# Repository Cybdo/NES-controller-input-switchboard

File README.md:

# NES-controller-input-switchboard
The switchboard is essentially a 2:2 6-channel multiplexer, with one output being routed to an RP2040 for processing and a USB Keyboard output as opposed to exposing it directly.
Part of a larger homemade arcade project, I want to be able to have a embedded controller with arcade buttons and an external connector for external controllers or a light zapper, to be routed to an NES for retro games, as well as a ZimaBoard or Pi 4 (or other computer, via USB) for modern games

## Features:
- 6 channel 2:2 multiplexer
- ability to switch a power line
- NES Controller signal decode
- USB-HID keyboard output for decoded signals
- Separate data and power USB-C connectors
- ~~Exposed GPIO for expansion~~

## Schematics

## Board

## Firmware
Thanks to [Print 'N Play](https://www.youtube.com/@PrintNPlay) ([Github](https://github.com/printnplay)) for opensourcing a [CircuitPython Script](https://github.com/printnplay/Pico-MicroPython/blob/main/NES2USB.py) that already performs my desired functionailty. If I feel up to it I may rewrite it myself in the future.

## JLCPCB order

## Credits
This project uses work from:
- [Kicad](https://www.kicad.org/)
- [CircuitPython](https://circuitpython.org/)
- [Print 'N Play](https://github.com/printnplay)
- [Hack Club!](https://hackclub.com)

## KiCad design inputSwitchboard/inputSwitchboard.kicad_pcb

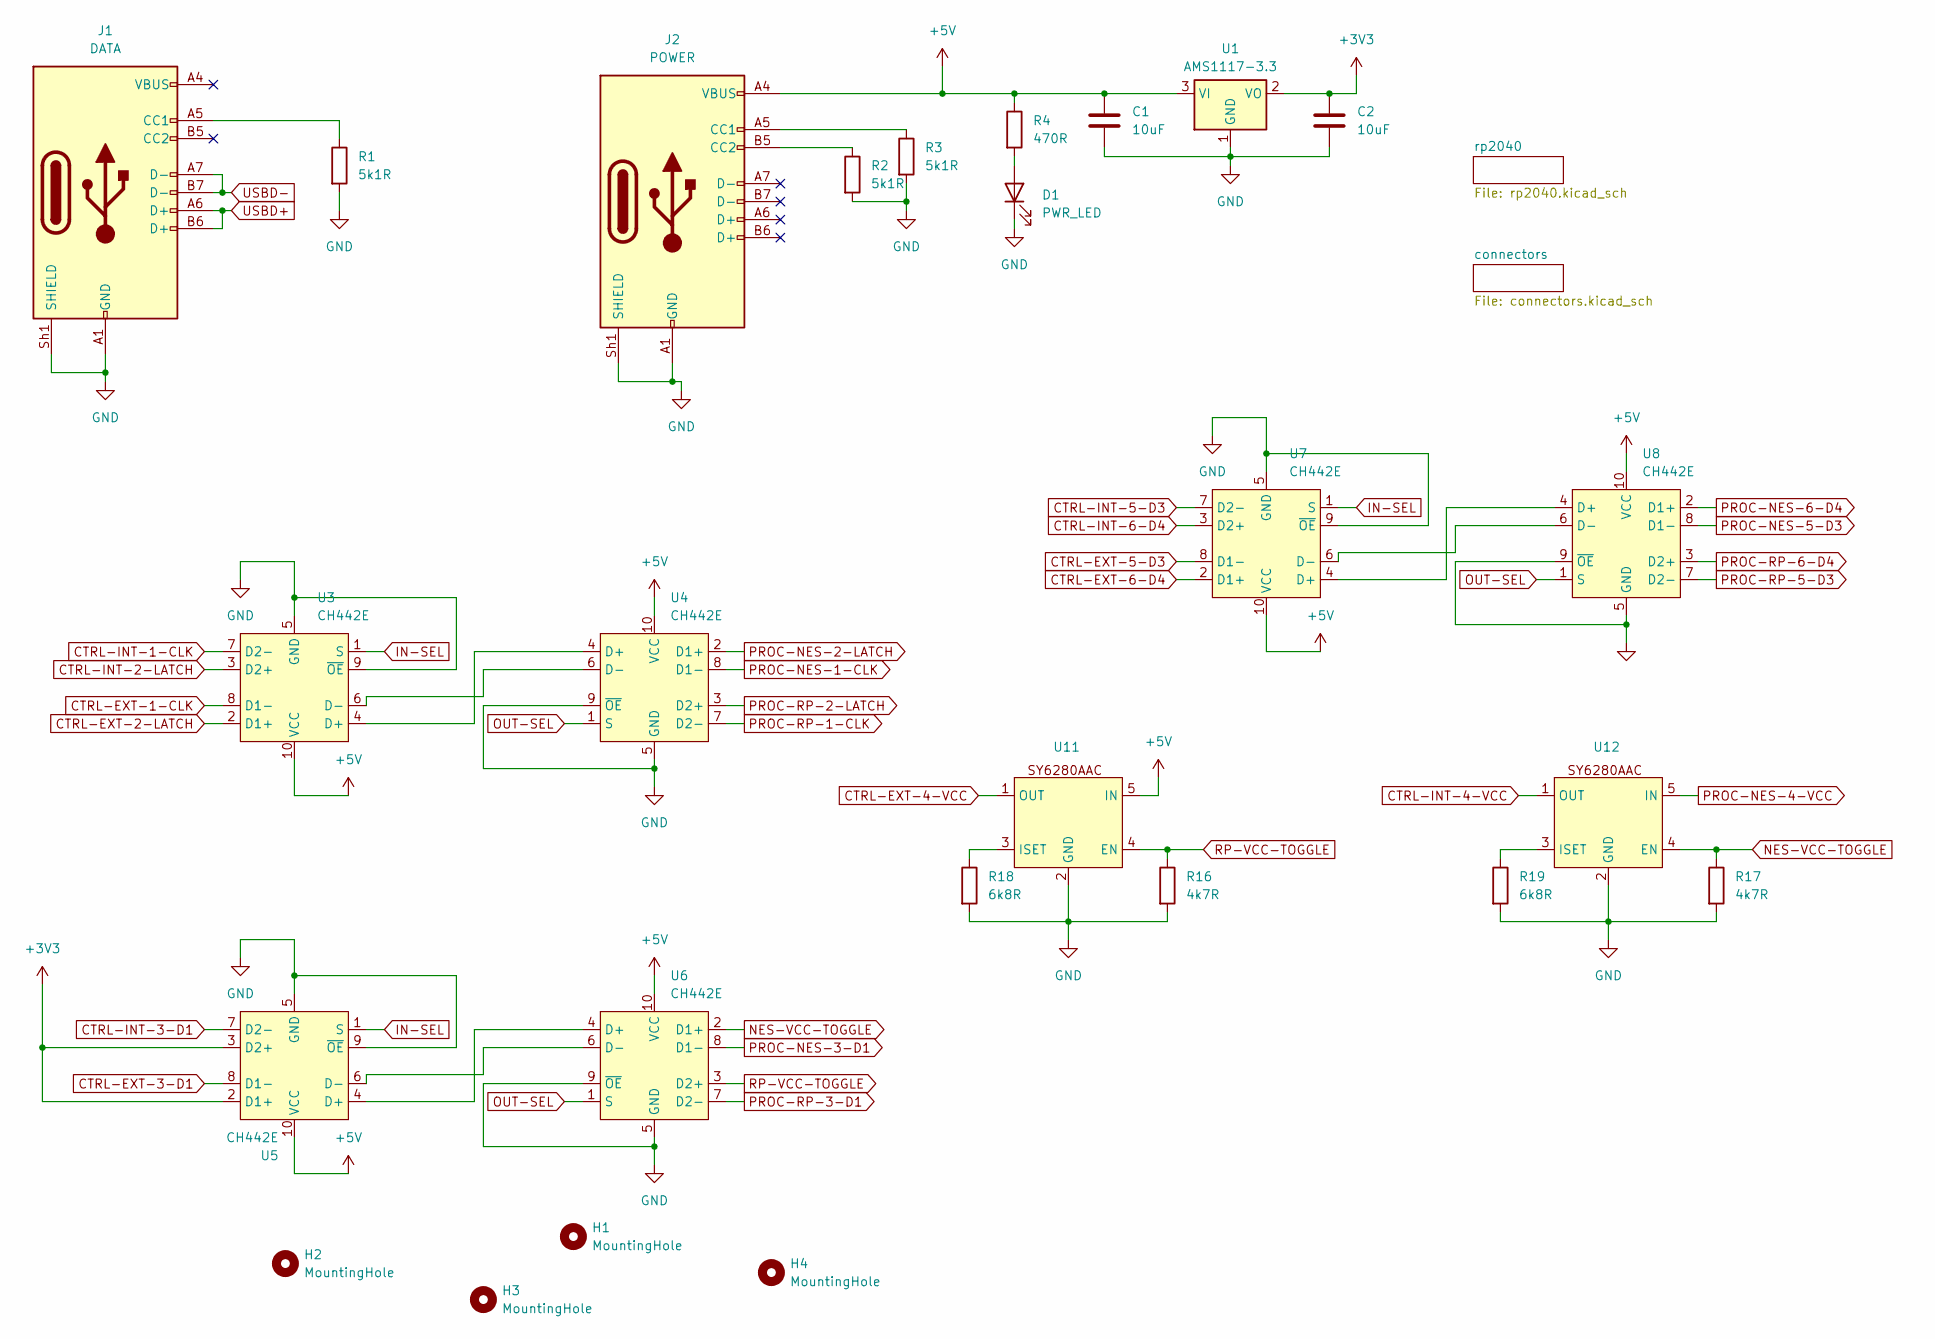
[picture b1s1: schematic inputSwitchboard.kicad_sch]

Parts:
C1, C2: 10uF; C_0201_0603Metric
D1: PWR_LED; LED_0603_1608Metric
H1, H2, H3, H4: MountingHole; MountingHole_4.3mm_M4
J1: DATA; TYPE-C-31-M-12
J2: POWER; TYPE-C-31-M-12
R1, R2, R3: 5k1R; R_0603_1608Metric
R4: 470R; R_0603_1608Metric
R16, R17: 4k7R; R_0603_1608Metric
R18, R19: 6k8R; R_0603_1608Metric
U1: AMS1117-3.3; SOT-223-3_TabPin2
U3, U4, U5, U6, U7, U8: CH442E; VSSOP-10_3x3mm_P0.5mm
U11, U12: SOT-23-5

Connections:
+3V3: C2.1, U1.2 (VO), U5.2 (D1+), U5.3 (D2+); also elsewhere on the board
+5V: C1.1, J2.A4 (VBUS), J2.A9 (VBUS), J2.B4 (VBUS), J2.B9 (VBUS), R4.1, U1.3 (VI), U3.10 (VCC), U4.10 (VCC), U5.10 (VCC), U6.10 (VCC), U7.10 (VCC), U8.10 (VCC), U11.5 (IN); also elsewhere on the board
CTRL-EXT-1-CLK: U3.8 (D1-); also elsewhere on the board
CTRL-EXT-2-LATCH: U3.2 (D1+); also elsewhere on the board
CTRL-EXT-3-D1: U5.8 (D1-); also elsewhere on the board
CTRL-EXT-4-VCC: U11.1 (OUT); also elsewhere on the board
CTRL-EXT-5-D3: U7.8 (D1-); also elsewhere on the board
CTRL-EXT-6-D4: U7.2 (D1+); also elsewhere on the board
CTRL-INT-1-CLK: U3.7 (D2-); also elsewhere on the board
CTRL-INT-2-LATCH: U3.3 (D2+); also elsewhere on the board
CTRL-INT-3-D1: U5.7 (D2-); also elsewhere on the board
CTRL-INT-4-VCC: U12.1 (OUT); also elsewhere on the board
CTRL-INT-5-D3: U7.7 (D2-); also elsewhere on the board
CTRL-INT-6-D4: U7.3 (D2+); also elsewhere on the board
GND: C1.2, C2.2, D1.1 (K), J1.A1 (GND), J1.A12 (GND), J1.B1 (GND), J1.B12 (GND), J1.Sh1 (SHIELD), J2.A1 (GND), J2.A12 (GND), J2.B1 (GND), J2.B12 (GND), J2.Sh1 (SHIELD), R1.2, R2.2, R3.2, R16.2, R17.2, R18.2, R19.2, U1.1 (GND), U3.5 (GND), U3.9 (~OE), U4.5 (GND), U4.9 (~OE), U5.5 (GND), U5.9 (~OE), U6.5 (GND), U6.9 (~OE), U7.5 (GND), U7.9 (~OE), U8.5 (GND), U8.9 (~OE), U11.2 (GND), U12.2 (GND); also elsewhere on the board
IN-SEL: U3.1 (S), U5.1 (S), U7.1 (S); also elsewhere on the board
NES-VCC-TOGGLE: R17.1, U6.2 (D1+), U12.4 (EN)
unnamed: D1.2 (A), R4.2
unnamed: J1.A5 (CC1), R1.1
unnamed: J2.A5 (CC1), R3.1
unnamed: J2.B5 (CC2), R2.1
unnamed: U3.4 (D+), U4.4 (D+)
unnamed: U3.6 (D-), U4.6 (D-)
unnamed: U5.4 (D+), U6.4 (D+)
unnamed: U5.6 (D-), U6.6 (D-)
unnamed: U7.4 (D+), U8.4 (D+)
unnamed: U7.6 (D-), U8.6 (D-)
unnamed: R18.1, U11.3 (ISET)
unnamed: R19.1, U12.3 (ISET)
OUT-SEL: U4.1 (S), U6.1 (S), U8.1 (S); also elsewhere on the board
PROC-NES-1-CLK: U4.8 (D1-); also elsewhere on the board
PROC-NES-2-LATCH: U4.2 (D1+); also elsewhere on the board
PROC-NES-3-D1: U6.8 (D1-); also elsewhere on the board
PROC-NES-4-VCC: U12.5 (IN); also elsewhere on the board
PROC-NES-5-D3: U8.8 (D1-); also elsewhere on the board
PROC-NES-6-D4: U8.2 (D1+); also elsewhere on the board
PROC-RP-1-CLK: U4.7 (D2-); also elsewhere on the board
PROC-RP-2-LATCH: U4.3 (D2+); also elsewhere on the board
PROC-RP-3-D1: U6.7 (D2-); also elsewhere on the board
PROC-RP-5-D3: U8.7 (D2-); also elsewhere on the board
PROC-RP-6-D4: U8.3 (D2+); also elsewhere on the board
RP-VCC-TOGGLE: R16.1, U6.3 (D2+), U11.4 (EN)
USBD+: J1.A6 (D+), J1.B6 (D+); also elsewhere on the board
USBD-: J1.A7 (D-), J1.B7 (D-); also elsewhere on the board

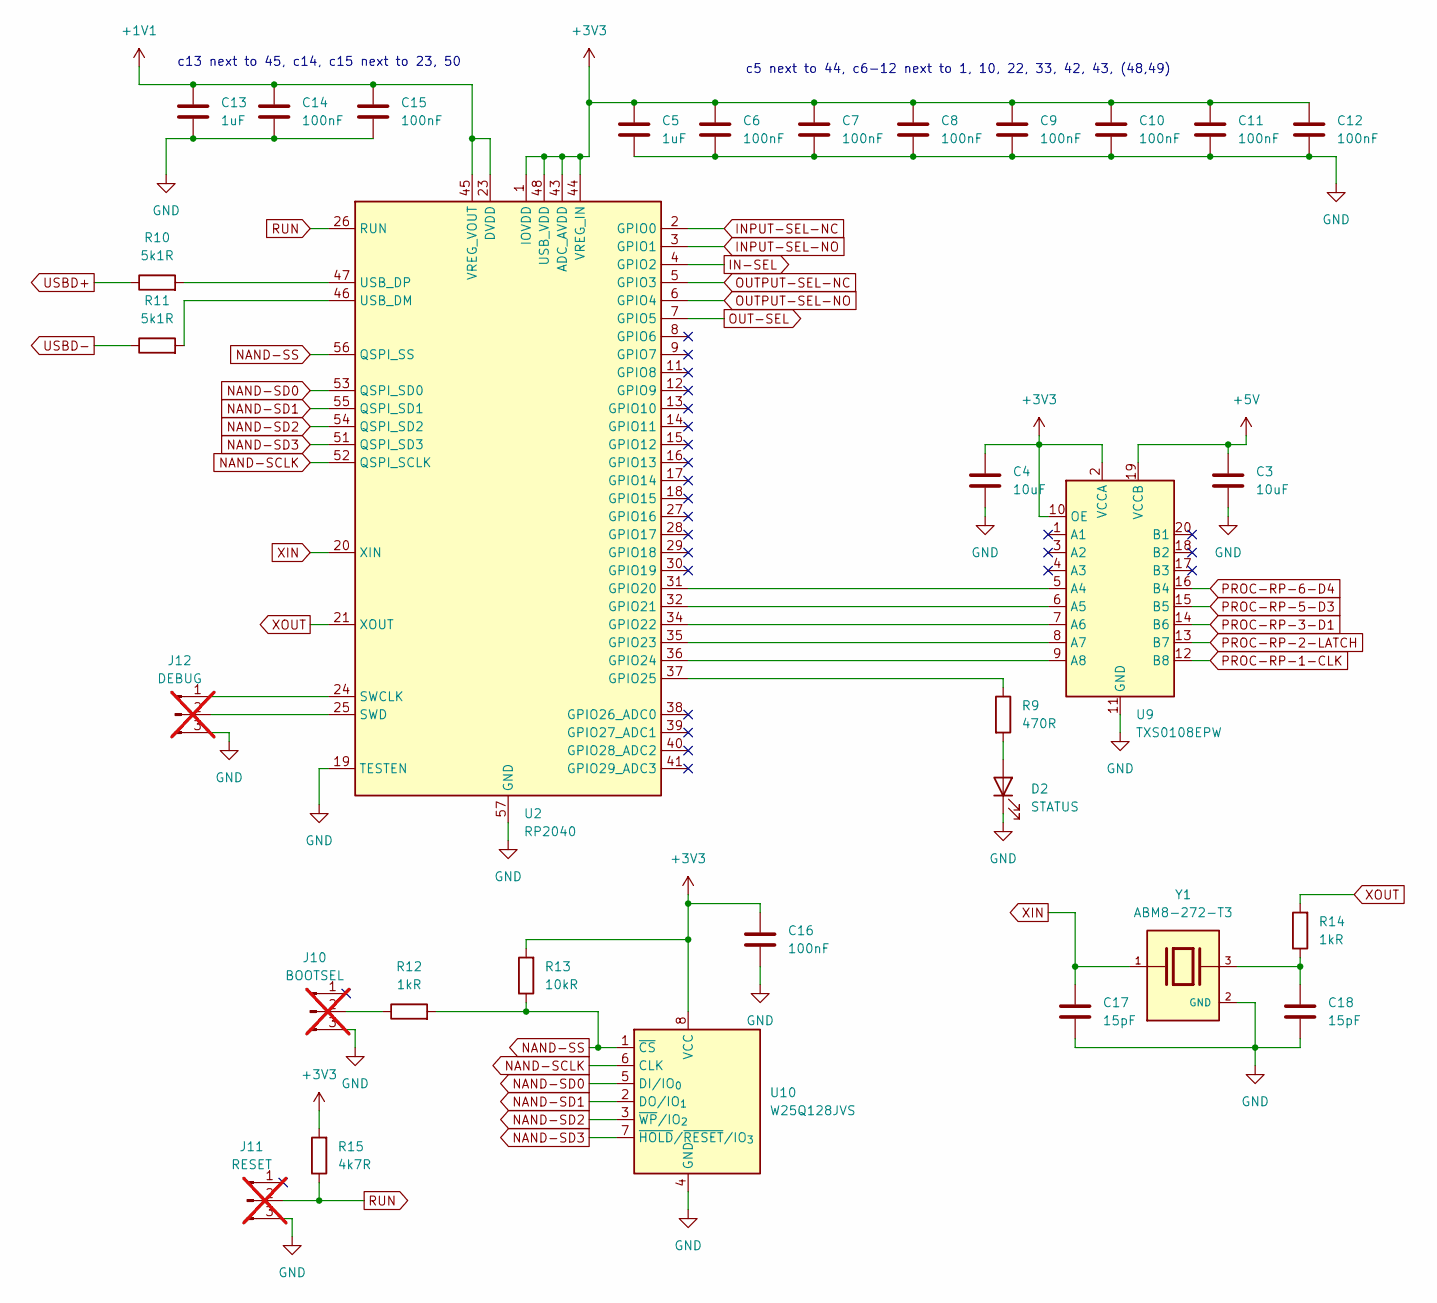
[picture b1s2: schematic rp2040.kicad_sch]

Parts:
C3, C4: 10uF; C_0201_0603Metric
C5, C13: 1uF; C_0201_0603Metric
C6, C7, C8, C9, C10, C11, C12, C14, C15, C16: 100nF; C_0201_0603Metric
C17, C18: 15pF; C_0201_0603Metric
D2: STATUS; LED_0603_1608Metric
J10: BOOTSEL; FanPinHeader_1x03_P2.54mm_Vertical; not fitted
J11: RESET; FanPinHeader_1x03_P2.54mm_Vertical; not fitted
J12: DEBUG; FanPinHeader_1x03_P2.54mm_Vertical; not fitted
R9: 470R; R_0603_1608Metric
R10, R11: 5k1R; R_0603_1608Metric
R12, R14: 1kR; R_0603_1608Metric
R13: 10kR; R_0603_1608Metric
R15: 4k7R; R_0603_1608Metric
U2: RP2040; QFN-56-1EP_7x7mm_P0.4mm_EP3.2x3.2mm
U9: TXS0108EPW; TSSOP-20_4.4x6.5mm_P0.65mm
U10: W25Q128JVS; SOIC-8_5.3x5.3mm_P1.27mm
Y1: ABM8-272-T3; XTAL_ABM8-272-T3; PARTREV 07-29-20

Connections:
+1V1: C13.1, C14.1, C15.1, U2.23 (DVDD), U2.45 (VREG_VOUT), U2.50 (DVDD)
+3V3: C4.1, C5.1, C6.1, C7.1, C8.1, C9.1, C10.1, C11.1, C12.1, C16.1, R13.2, R15.2, U2.1 (IOVDD), U2.10 (IOVDD), U2.22 (IOVDD), U2.33 (IOVDD), U2.42 (IOVDD), U2.43 (ADC_AVDD), U2.44 (VREG_IN), U2.48 (USB_VDD), U2.49 (IOVDD), U9.2 (VCCA), U9.10 (OE), U10.8 (VCC); also elsewhere on the board
+5V: C3.1, U9.19 (VCCB); also elsewhere on the board
GND: C3.2, C4.2, C5.2, C6.2, C7.2, C8.2, C9.2, C10.2, C11.2, C12.2, C13.2, C14.2, C15.2, C16.2, C17.2, C18.2, D2.1 (K), J10.3, J11.3, J12.3, U2.19 (TESTEN), U2.57 (GND), U9.11 (GND), U10.4 (GND), Y1.2 (GND), Y1.4 (GND); also elsewhere on the board
IN-SEL: U2.4 (GPIO2); also elsewhere on the board
INPUT-SEL-NC: U2.2 (GPIO0); also elsewhere on the board
INPUT-SEL-NO: U2.3 (GPIO1); also elsewhere on the board
NAND-SCLK: U2.52 (QSPI_SCLK), U10.6 (CLK)
NAND-SD0: U2.53 (QSPI_SD0), U10.5 (DI/IO_{0})
NAND-SD1: U2.55 (QSPI_SD1), U10.2 (DO/IO_{1})
NAND-SD2: U2.54 (QSPI_SD2), U10.3 (~WP/IO_{2})
NAND-SD3: U2.51 (QSPI_SD3), U10.7 (~HOLD/~RESET/IO_{3})
NAND-SS: R12.2, R13.1, U2.56 (QSPI_SS), U10.1 (~CS)
unnamed: C18.1, R14.1, Y1.3
unnamed: D2.2 (A), R9.2
unnamed: J10.2, R12.1
unnamed: J12.1, U2.24 (SWCLK)
unnamed: J12.2, U2.25 (SWD)
unnamed: U2.31 (GPIO20), U9.5 (A4)
unnamed: U2.32 (GPIO21), U9.6 (A5)
unnamed: U2.34 (GPIO22), U9.7 (A6)
unnamed: U2.35 (GPIO23), U9.8 (A7)
unnamed: U2.36 (GPIO24), U9.9 (A8)
unnamed: R9.1, U2.37 (GPIO25)
unnamed: R11.2, U2.46 (USB_DM)
unnamed: R10.2, U2.47 (USB_DP)
OUT-SEL: U2.7 (GPIO5); also elsewhere on the board
OUTPUT-SEL-NC: U2.5 (GPIO3); also elsewhere on the board
OUTPUT-SEL-NO: U2.6 (GPIO4); also elsewhere on the board
PROC-RP-1-CLK: U9.12 (B8); also elsewhere on the board
PROC-RP-2-LATCH: U9.13 (B7); also elsewhere on the board
PROC-RP-3-D1: U9.14 (B6); also elsewhere on the board
PROC-RP-5-D3: U9.15 (B5); also elsewhere on the board
PROC-RP-6-D4: U9.16 (B4); also elsewhere on the board
RUN: J11.2, R15.1, U2.26 (RUN)
USBD+: R10.1; also elsewhere on the board
USBD-: R11.1; also elsewhere on the board
XIN: C17.1, U2.20 (XIN), Y1.1
XOUT: R14.2, U2.21 (XOUT)

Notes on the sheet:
c5 next to 44, c6-12 next to 1, 10, 22, 33, 42, 43, (48,49)
c13 next to 45, c14, c15 next to 23, 50

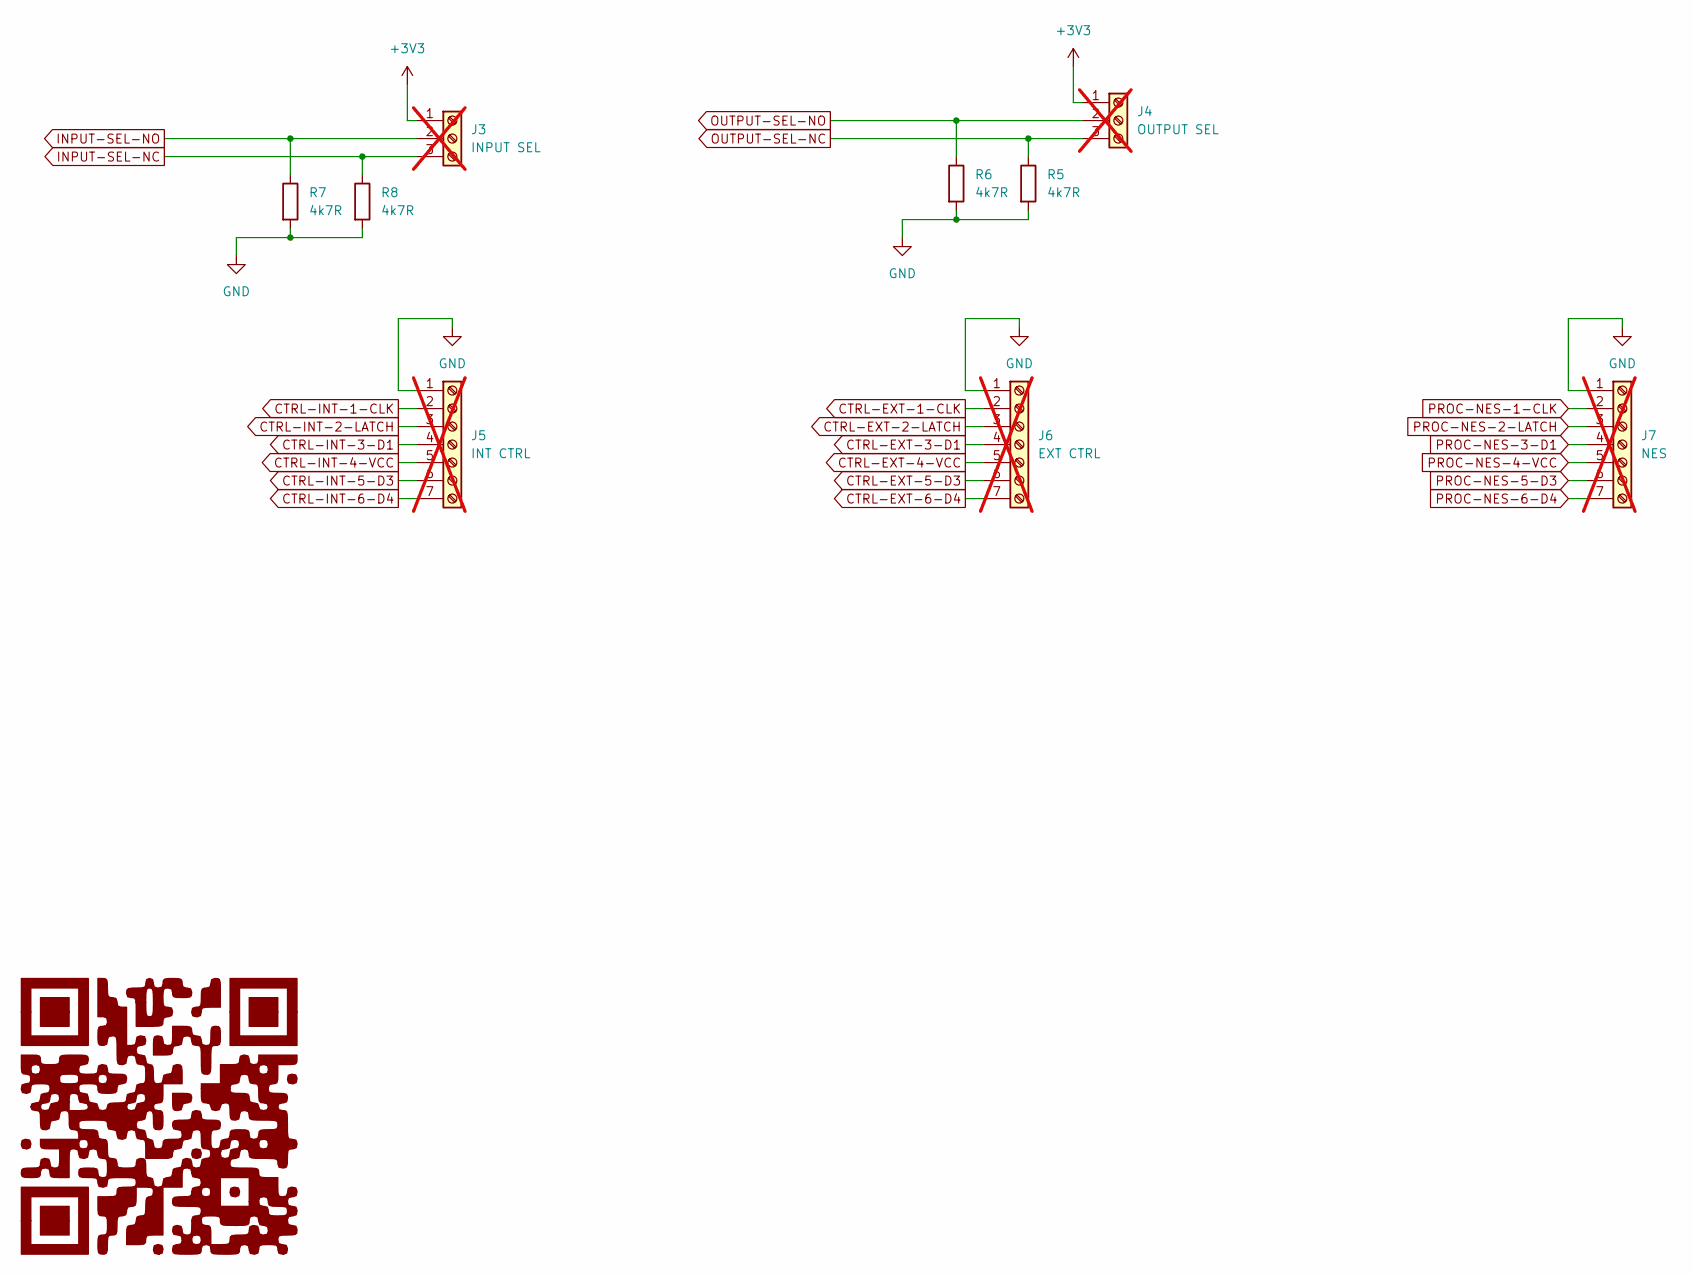
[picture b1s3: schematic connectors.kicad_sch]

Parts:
J3: INPUT SEL; TerminalBlock_Phoenix_MKDS-1,5-3-5.08_1x03_P5.08mm_Horizont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; not fitted
J4: OUTPUT SEL; TerminalBlock_Phoenix_MKDS-1,5-3-5.08_1x03_P5.08mm_Horizont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; not fitted
J5: INT CTRL; TerminalBlock_MaiXu_MX126-5.0-07P_1x07_P5.00mm; not fitted
J6: EXT CTRL; TerminalBlock_MaiXu_MX126-5.0-07P_1x07_P5.00mm; not fitted
J7: NES; TerminalBlock_MaiXu_MX126-5.0-07P_1x07_P5.00mm; not fitted
R5, R6, R7, R8: 4k7R; R_0603_1608Metric

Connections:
+3V3: J3.1, J4.1; also elsewhere on the board
CTRL-EXT-1-CLK: J6.2; also elsewhere on the board
CTRL-EXT-2-LATCH: J6.3; also elsewhere on the board
CTRL-EXT-3-D1: J6.4; also elsewhere on the board
CTRL-EXT-4-VCC: J6.5; also elsewhere on the board
CTRL-EXT-5-D3: J6.6; also elsewhere on the board
CTRL-EXT-6-D4: J6.7; also elsewhere on the board
CTRL-INT-1-CLK: J5.2; also elsewhere on the board
CTRL-INT-2-LATCH: J5.3; also elsewhere on the board
CTRL-INT-3-D1: J5.4; also elsewhere on the board
CTRL-INT-4-VCC: J5.5; also elsewhere on the board
CTRL-INT-5-D3: J5.6; also elsewhere on the board
CTRL-INT-6-D4: J5.7; also elsewhere on the board
GND: J5.1, J6.1, J7.1, R5.2, R6.2, R7.2, R8.2; also elsewhere on the board
INPUT-SEL-NC: J3.3, R8.1; also elsewhere on the board
INPUT-SEL-NO: J3.2, R7.1; also elsewhere on the board
OUTPUT-SEL-NC: J4.3, R5.1; also elsewhere on the board
OUTPUT-SEL-NO: J4.2, R6.1; also elsewhere on the board
PROC-NES-1-CLK: J7.2; also elsewhere on the board
PROC-NES-2-LATCH: J7.3; also elsewhere on the board
PROC-NES-3-D1: J7.4; also elsewhere on the board
PROC-NES-4-VCC: J7.5; also elsewhere on the board
PROC-NES-5-D3: J7.6; also elsewhere on the board
PROC-NES-6-D4: J7.7; also elsewhere on the board

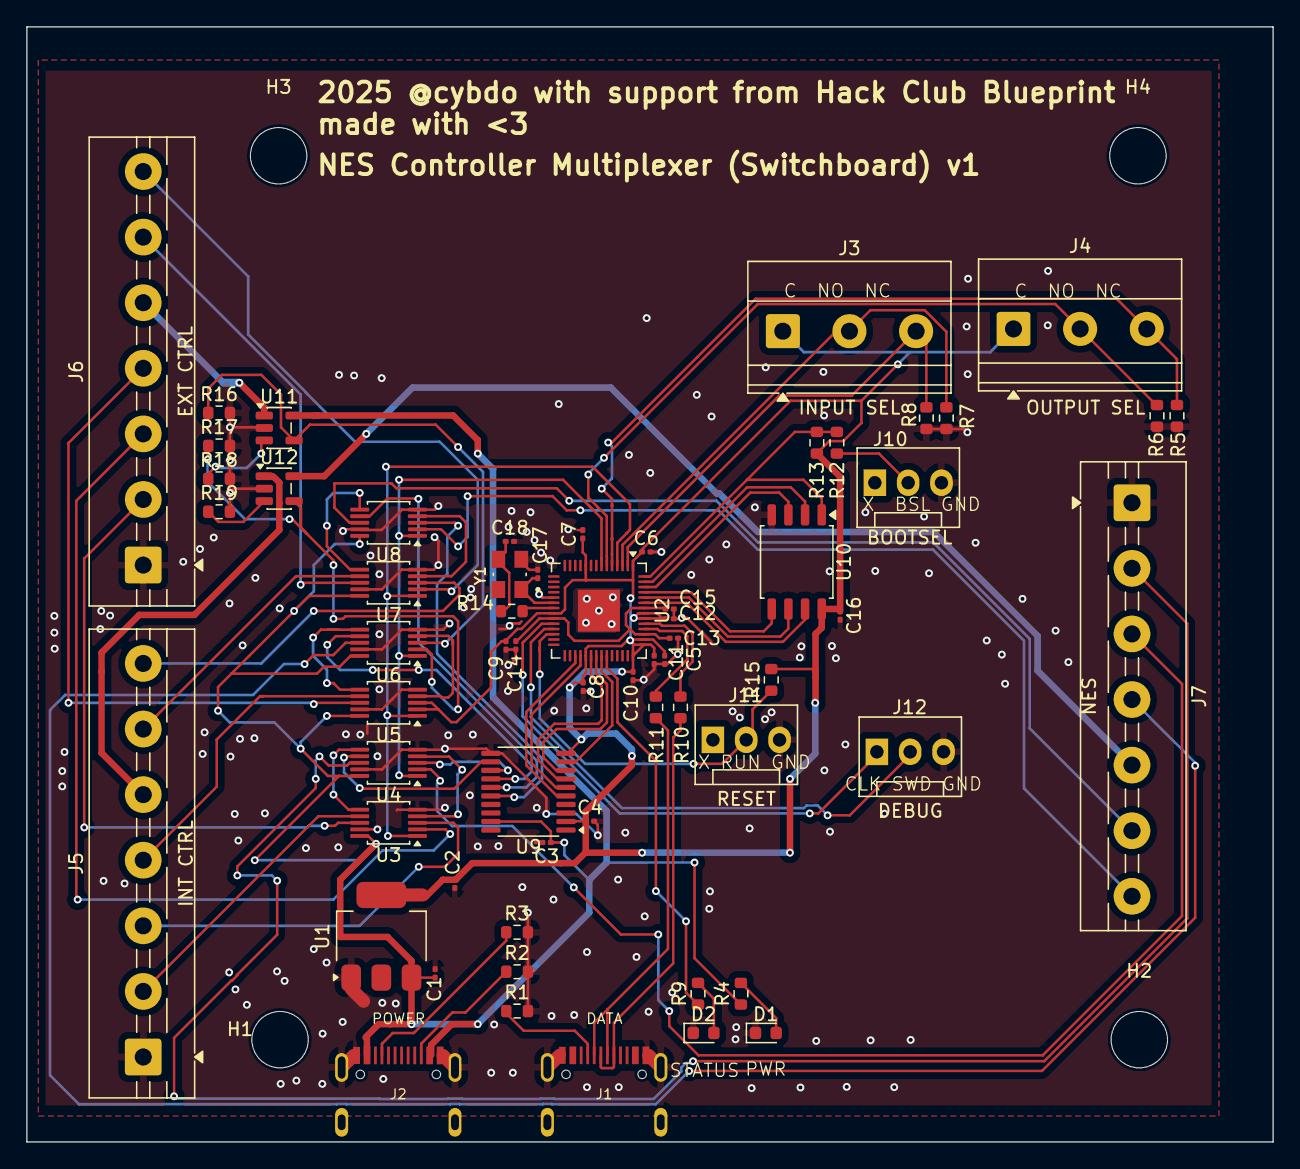
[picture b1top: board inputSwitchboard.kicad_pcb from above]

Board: 2 copper layers, 95.0 x 85.0 mm, 66 parts (0 on the bottom side), 71 nets.

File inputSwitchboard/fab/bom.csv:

Id,Designator,Footprint,Quantity,Comment,Supplier and ref
1,",",,2,,
2,"C5,C13",C_0201_0603Metric,2,1uF,
3,"C11,C15,C16,C12,C6,C10,C8,C14,C9,C7",C_0201_0603Metric,10,100nF,
4,"C17,C18",C_0201_0603Metric,2,15pF,
5,Y1,XTAL_ABM8-272-T3,1,ABM8-272-T3,
6,J1,TYPE-C-31-M-12,1,DATA,
7,"R6,R17,R7,R5,R8,R15,R16",R_0603_1608Metric,7,4k7R,
8,U9,TSSOP-20_4.4x6.5mm_P0.65mm,1,TXS0108EPW,
9,J2,TYPE-C-31-M-12,1,POWER,
10,"C2,C1,C4,C3",C_0201_0603Metric,4,10uF,
11,"R11,R3,R1,R10,R2",R_0603_1608Metric,5,5k1R,
12,D2,LED_0201_0603Metric,1,STATUS,
13,"R19,R18",R_0603_1608Metric,2,6k8R,
14,"U4,U8,U3,U7,U5,U6",MSOP-10-1EP_3x3mm_P0.5mm_EP1.68x1.88mm,6,CH442E,
15,"R9,R4",R_0603_1608Metric,2,470R,
16,"R12,R14",R_0603_1608Metric,2,1kR,
17,"U12,U11",SOT-23-5,2,~,
18,U10,SOIC-8_5.3x5.3mm_P1.27mm,1,W25Q128JVS,
19,U2,QFN-56-1EP_7x7mm_P0.4mm_EP3.2x3.2mm,1,RP2040,
20,D1,LED_0201_0603Metric,1,PWR_LED,
21,R13,R_0603_1608Metric,1,10kR,
22,U1,SOT-223-3_TabPin2,1,AMS1117-3.3,

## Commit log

2025-12-03 journal 2
2025-12-05 finished schematic
2025-12-06 Proofread, started to route
2025-12-07 finished routing
2025-12-07 fixed more stuff and polished routing
2025-12-07 start of a README
2025-12-14 done!
2025-12-14 update manufacture files, create BOM
2025-12-26 csvs got gitignored :sob:
